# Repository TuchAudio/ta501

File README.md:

# ta501
Input Selector Board

## Purpose
Basic input board for **[TuchAudio 303](../../../ta303) integrated amplifier**, a.k.a. _The Bedroom Amp_, together with:

- [TuchAudio 103](../../../ta103): Phono pre-amp.
- [TuchAudio 202](../../../ta202): compact power amp.
- A generic **12V/2A power supply**

## Inputs

- **Phono:** 3.6 mV / 110 kohm. (via the [103 pre-amp](../../../ta103), otherwise same as line input)
- **Line:** 180 mV / 900 kohm.
- **Tape Playback:** thru RCA (180 mV/47 k) and DIN (0.48 V/16.5 k) connectors.

## Outputs

- Line out: 180 mV (intended for a suitable poweramp, like [TuchAudio 202](../../../ta202)).
- Tape Rec (RCA): 180 mV
- Tape Rec (DIN): 5.3 mV over 10 kohm

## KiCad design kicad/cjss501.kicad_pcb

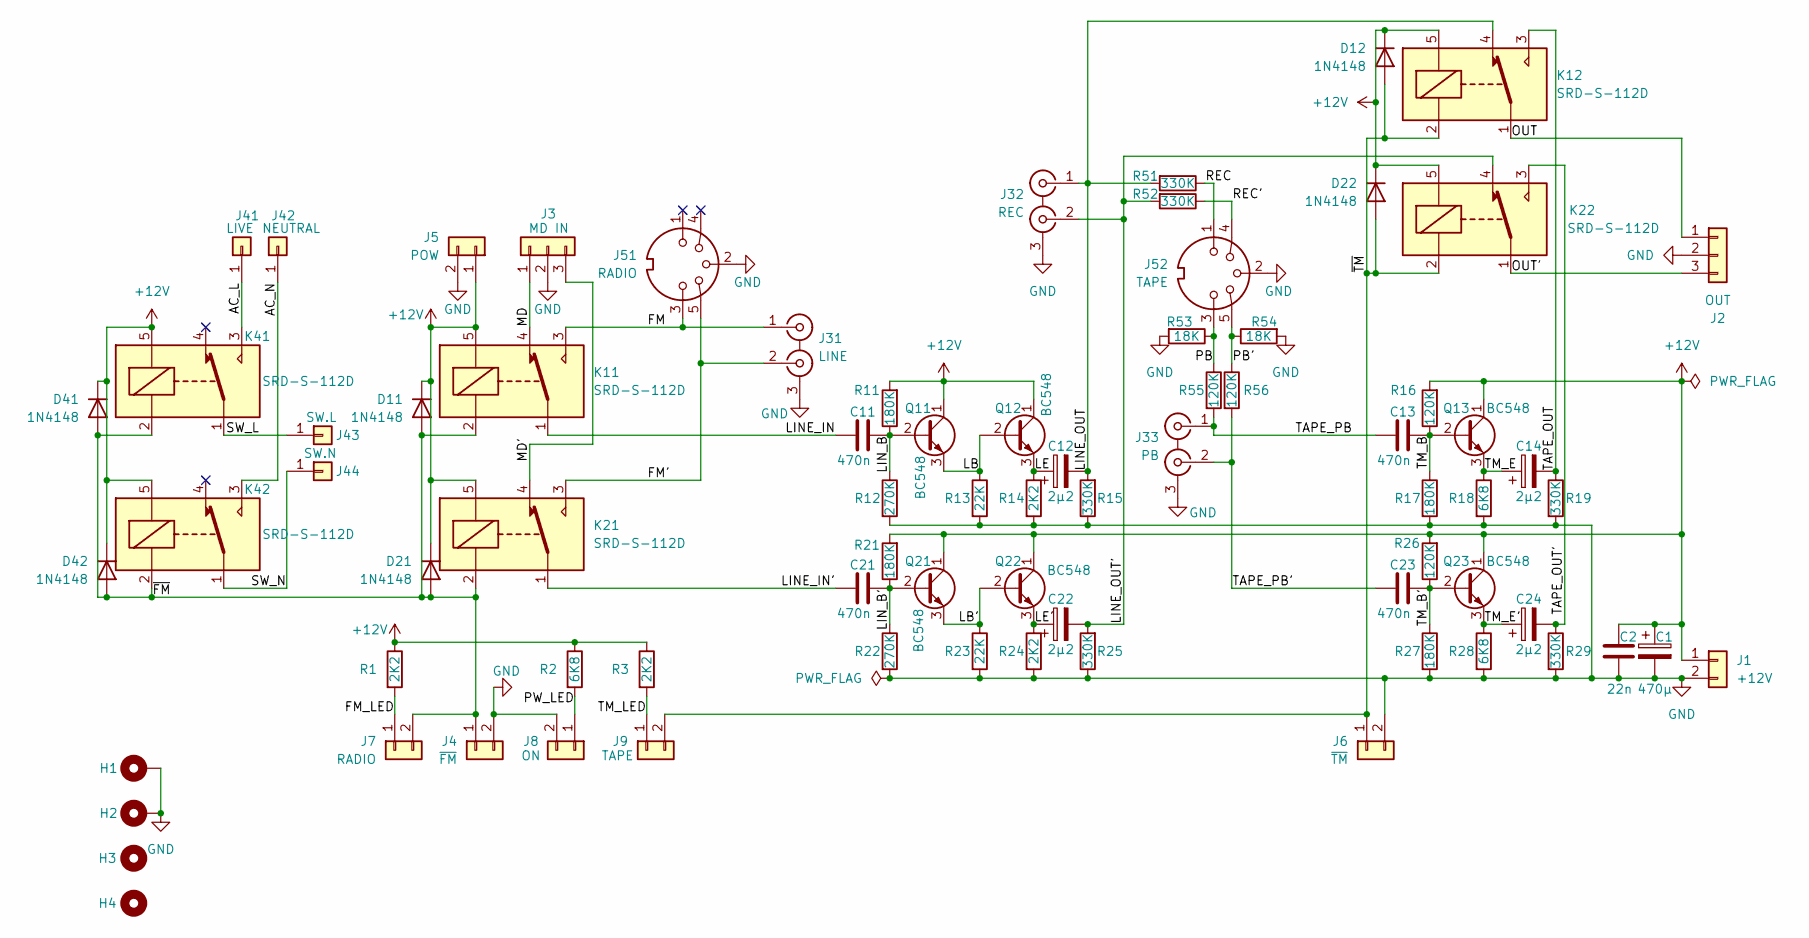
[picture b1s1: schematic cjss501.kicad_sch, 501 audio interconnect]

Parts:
C1: 470µ; CP_Radial_D6.3mm_P2.50mm
C2: 22n; C_Disc_D6.0mm_W2.5mm_P5.00mm
C11, C13, C21, C23: 470n; C_Rect_L7.2mm_W3.0mm_P5.00mm_FKS2_FKP2_MKS2_MKP2
C12, C14, C22, C24: 2µ2; CP_Radial_D4.0mm_P1.50mm
D11, D12, D21, D22, D41, D42: 1N4148; D_DO-35_SOD27_P7.62mm_Horizontal
H1, H2: MountingHole_Pad; MountingHole_3.2mm_M3_DIN965_Pad
H3, H4: MountingHole; MountingHole_3.2mm_M3
J1: +12V; PinHeader_1x02_P2.54mm_Vertical
J2: OUT; PinHeader_1x03_P2.54mm_Vertical
J3: MD IN; PinHeader_1x03_P2.54mm_Vertical
J4: ~{FM}; PinHeader_1x02_P2.54mm_Vertical
J5: POW; PinHeader_1x02_P2.54mm_Vertical
J6: ~{TM}; PinHeader_1x02_P2.54mm_Vertical
J7: RADIO; PinHeader_1x02_P2.54mm_Vertical
J8: ON; PinHeader_1x02_P2.54mm_Vertical
J9: TAPE; PinHeader_1x02_P2.54mm_Vertical
J31: LINE; 2xRCA_vertical
J32: REC; 2xRCA_vertical
J33: PB; 2xRCA_vertical
J41: LIVE; PinHeader_1x01_P2.54mm_Vertical
J42: NEUTRAL; PinHeader_1x01_P2.54mm_Vertical
J43: SW.L; PinHeader_1x01_P2.54mm_Vertical
J44: SW.N; PinHeader_1x01_P2.54mm_Vertical
J51: RADIO; DIN 5-180deg
J52: TAPE; DIN 5-180deg
K11, K12, K21, K22, K41, K42: SRD-S-112D; Relay_SPDT_SANYOU_SRD_Series_Form_C
Q11, Q12, Q13, Q21, Q22, Q23: BC548; TO-92_Inline
R1, R3, R14, R24: 2K2; R_Axial_DIN0207_L6.3mm_D2.5mm_P2.54mm_Vertical
R2, R18, R28: 6K8; R_Axial_DIN0207_L6.3mm_D2.5mm_P2.54mm_Vertical
R11, R17, R21, R27: 180K; R_Axial_DIN0207_L6.3mm_D2.5mm_P2.54mm_Vertical
R12, R22: 270K; R_Axial_DIN0207_L6.3mm_D2.5mm_P2.54mm_Vertical
R13, R23: 22K; R_Axial_DIN0207_L6.3mm_D2.5mm_P2.54mm_Vertical
R15, R19, R25, R29, R51, R52: 330K; R_Axial_DIN0207_L6.3mm_D2.5mm_P2.54mm_Vertical
R16, R26, R55, R56: 120K; R_Axial_DIN0207_L6.3mm_D2.5mm_P2.54mm_Vertical
R53, R54: 18K; R_Axial_DIN0207_L6.3mm_D2.5mm_P2.54mm_Vertical

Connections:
+12V: C1.1, C2.1, D11.1 (K), D12.1 (K), D21.1 (K), D22.1 (K), D41.1 (K), D42.1 (K), J1.1, J5.1, K11.5, K12.5, K21.5, K22.5, K41.5, K42.5, Q11.1 (C), Q12.1 (C), Q13.1 (C), Q21.1 (C), Q22.1 (C), Q23.1 (C), R1.1, R2.1, R3.1, R11.2, R16.2, R21.2, R26.2
/AC_L: J41.1, K41.3
/AC_N: J42.1, K42.3
/FM: J31.1 (IN1), J51.3, K11.3
/FM': J31.2 (IN2), J51.5, K21.3
/FM_LED: J7.1, R1.2
/LB: Q11.3 (E), Q12.2 (B), R13.1
/LB': Q21.3 (E), Q22.2 (B), R23.1
/LE: C12.1, Q12.3 (E), R14.1
/LE': C22.1, Q22.3 (E), R24.1
/LINE_IN: C11.1, K11.1
/LINE_IN': C21.1, K21.1
/LINE_OUT: C12.2, J32.1 (IN1), K12.4, R15.2, R51.2
/LINE_OUT': C22.2, J32.2 (IN2), K22.4, R25.2, R52.2
/LIN_B: C11.2, Q11.2 (B), R11.1, R12.1
/LIN_B': C21.2, Q21.2 (B), R21.1, R22.1
/MD: J3.1, K11.4
/MD': J3.3, K21.4
/OUT: J2.1, K12.1
/OUT': J2.3, K22.1
/PB: J52.3, R53.1, R55.1
/PB': J52.5, R54.1, R56.1
/PW_LED: J8.1, R2.2
/REC: J52.1, R51.1
/REC': J52.4, R52.1
/SW_L: J43.1, K41.1
/SW_N: J44.1, K42.1
/TAPE_OUT: C14.2, K12.3, R19.1
/TAPE_OUT': C24.2, K22.3, R29.1
/TAPE_PB: C13.1, J33.1 (IN1), R55.2
/TAPE_PB': C23.1, J33.2 (IN2), R56.2
/TM_B: C13.2, Q13.2 (B), R16.1, R17.1
/TM_B': C23.2, Q23.2 (B), R26.1, R27.1
/TM_E: C14.1, Q13.3 (E), R18.1
/TM_E': C24.1, Q23.3 (E), R28.1
/TM_LED: J9.1, R3.2
/~FM: D11.2 (A), D21.2 (A), D41.2 (A), D42.2 (A), J4.1, J7.2, K11.2, K21.2, K41.2, K42.2
/~TM: D12.2 (A), D22.2 (A), J6.1, J9.2, K12.2, K22.2
GND: C1.2, C2.2, H1.1, H2.1, J1.2, J2.2, J3.2, J4.2, J5.2, J6.2, J8.2, J31.3 (EXT), J32.3 (EXT), J33.3 (EXT), J51.2, J52.2, R12.2, R13.2, R14.2, R15.1, R17.2, R18.2, R19.2, R22.2, R23.2, R24.2, R25.1, R27.2, R28.2, R29.2, R53.2, R54.2

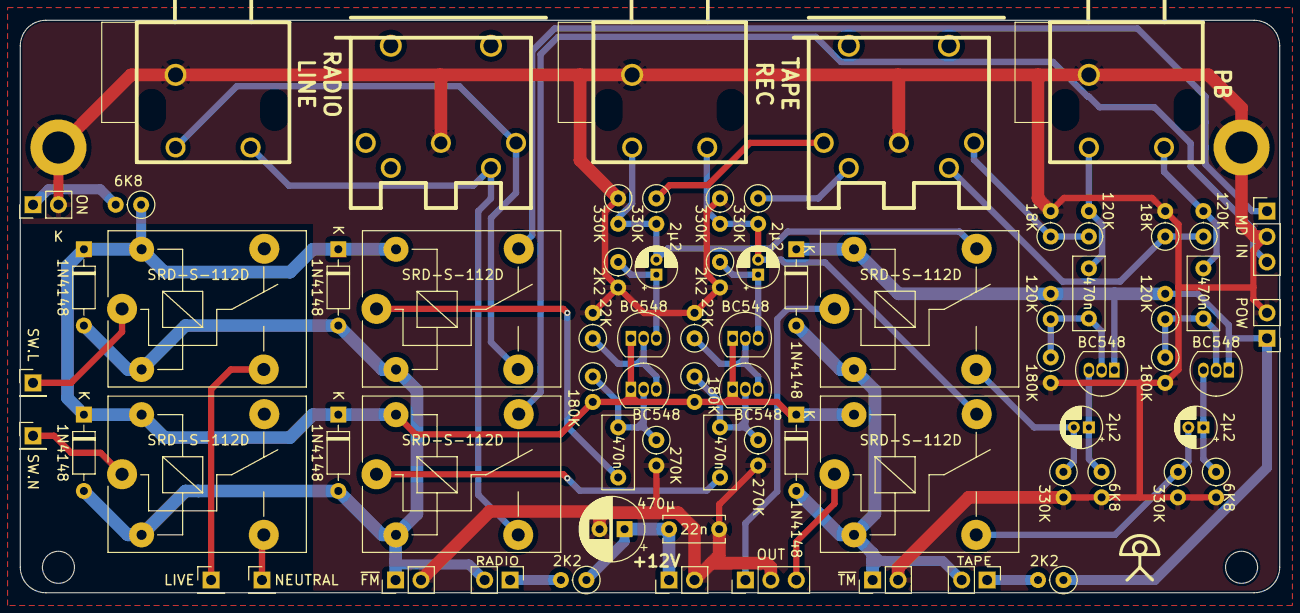
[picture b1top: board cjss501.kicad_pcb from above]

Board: 2 copper layers, 125.7 x 57.1 mm, 77 parts (0 on the bottom side), 39 nets.

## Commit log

2025-11-08 add KiCAD files
2025-11-11 Basic I/O specs
2025-11-24 fix inputs and outputs
2025-11-24 add links
